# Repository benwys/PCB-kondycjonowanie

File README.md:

# PCB-kondycjonowanie
Projekt układu kondycjonowania sygnałów pomiarowych dla falownika napięcia

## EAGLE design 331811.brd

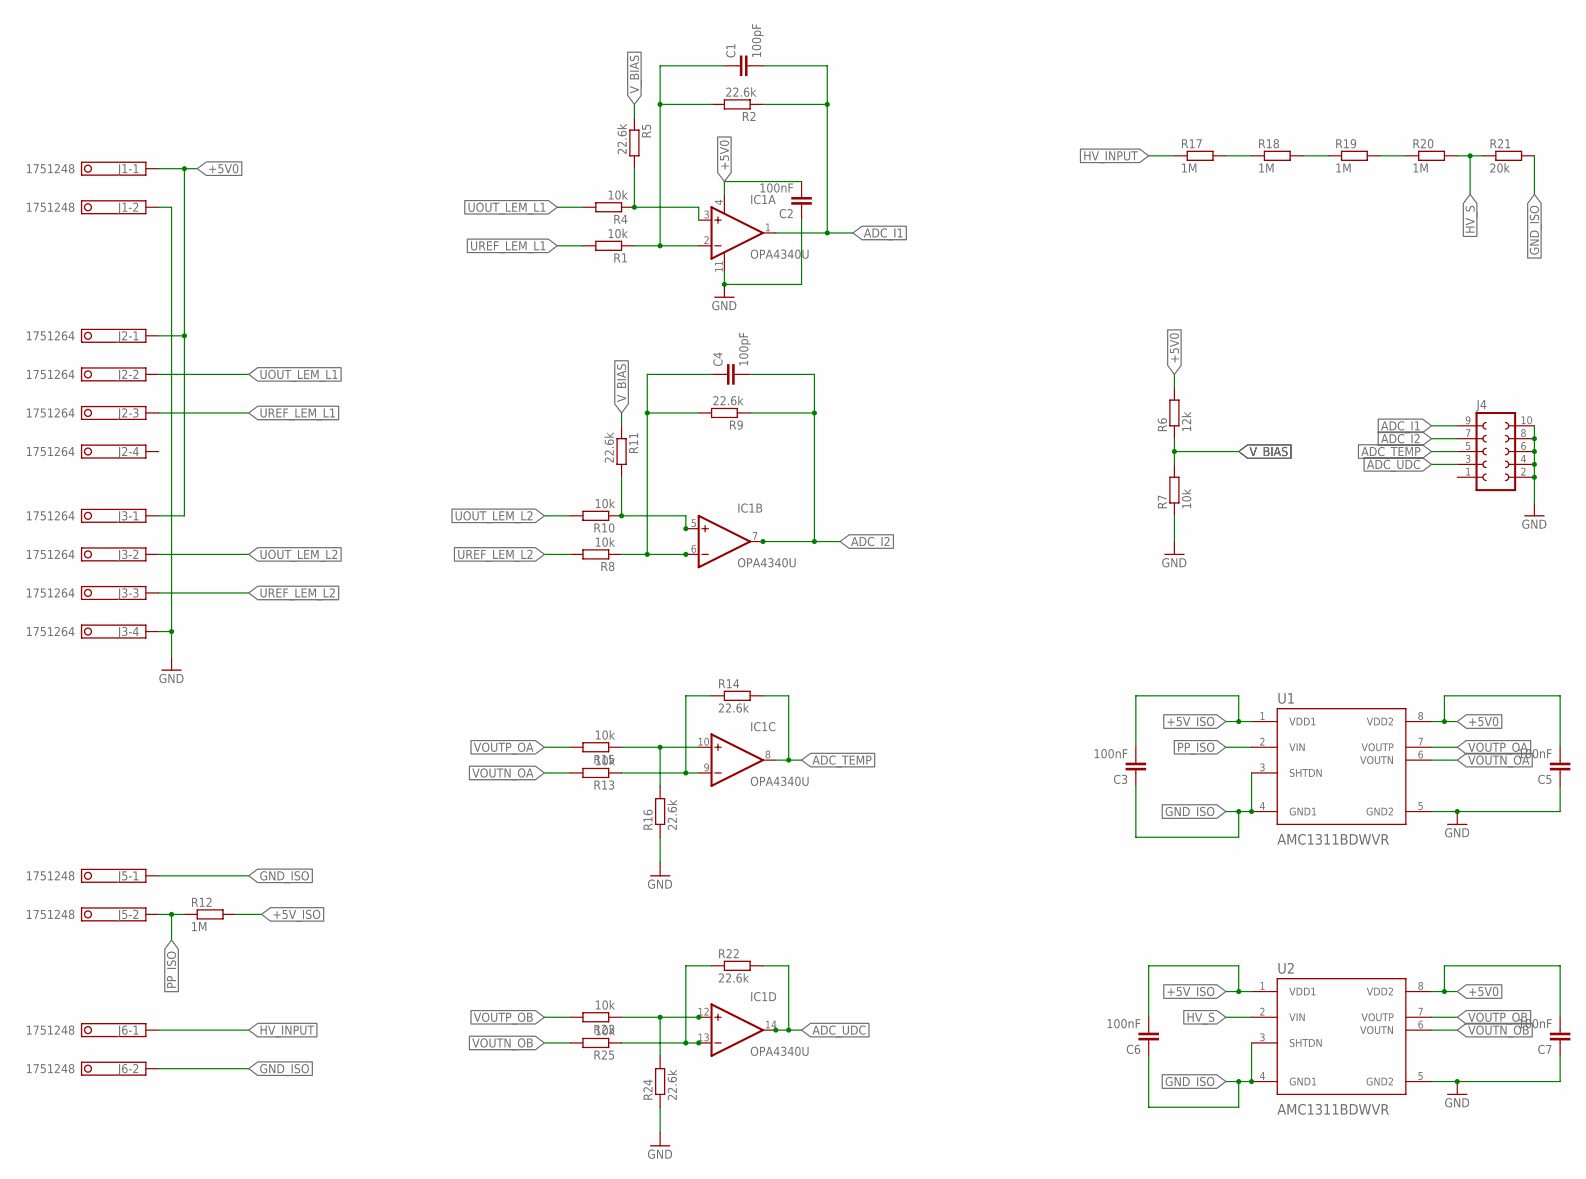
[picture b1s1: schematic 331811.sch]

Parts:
C1, C4: 100pF; C0805
C2, C3, C5, C6, C7: 100nF; C0805
IC1: OPA4340U; SO14
J1, J5, J6: 1751248
J2, J3: 1751264
J4: FE05-2
R1, R4, R7, R8, R10, R13, R15, R23, R25: 10k; M1206
R2, R5, R9, R11, R14, R16, R22, R24: 22.6k; M1206
R6: 12k; M1206
R12, R17, R18, R19, R20: 1M; M1206
R21: 20k; M1206
U1, U2: AMC1311BDWVR; SOIC127P1150X280-8N

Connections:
+5V0: C2.2, C5.2, C7.2, IC1.4 (V+), J1.1, J2.1, J3.1, R6.2, U1.8 (VDD2), U2.8 (VDD2)
+5V_ISO: C3.2, C6.2, R12.2, U1.1 (VDD1), U2.1 (VDD1)
ADC_I1: C1.2, IC1.1 (OUT), J4.9, R2.1
ADC_I2: C4.2, IC1.7 (OUT), J4.7, R9.1
ADC_TEMP: IC1.8 (OUT), J4.5, R14.2
ADC_UDC: IC1.14 (OUT), J4.3, R22.2
GND: C2.1, C5.1, C7.1, IC1.11 (V-), J1.2, J3.4, J4.2, J4.4, J4.6, J4.8, J4.10, R7.1, R16.1, R24.1, U1.5 (GND2), U2.5 (GND2)
GND_ISO: C3.1, C6.1, J5.1, J6.2, R21.2, U1.3 (SHTDN), U1.4 (GND1), U2.3 (SHTDN), U2.4 (GND1)
HV_INPUT: J6.1, R17.1
HV_S: R20.2, R21.1, U2.2 (VIN)
unnamed: C4.1, IC1.6 (-IN), R8.1, R9.2
unnamed: IC1.5 (+IN), R10.1, R11.2
unnamed: C1.1, IC1.2 (-IN), R1.1, R2.2
unnamed: IC1.9 (-IN), R13.1, R14.1
unnamed: IC1.3 (+IN), R4.1, R5.2
unnamed: IC1.10 (+IN), R15.1, R16.2
unnamed: R17.2, R18.1
unnamed: R18.2, R19.1
unnamed: R19.2, R20.1
unnamed: IC1.13 (-IN), R22.1, R25.1
unnamed: IC1.12 (+IN), R23.1, R24.2
PP_ISO: J5.2, R12.1, U1.2 (VIN)
UOUT_LEM_L1: J2.2
UOUT_LEM_L2: J3.2
UREF_LEM_L1: J2.3, R1.2
UREF_LEM_L2: J3.3, R8.2
VOUTN_OA: R13.2, U1.6 (VOUTN)
VOUTN_OB: R25.2, U2.6 (VOUTN)
VOUTP_OA: R15.2, U1.7 (VOUTP)
VOUTP_OB: R23.2, U2.7 (VOUTP)
V_BIAS: R5.1, R6.1, R7.2, R11.1

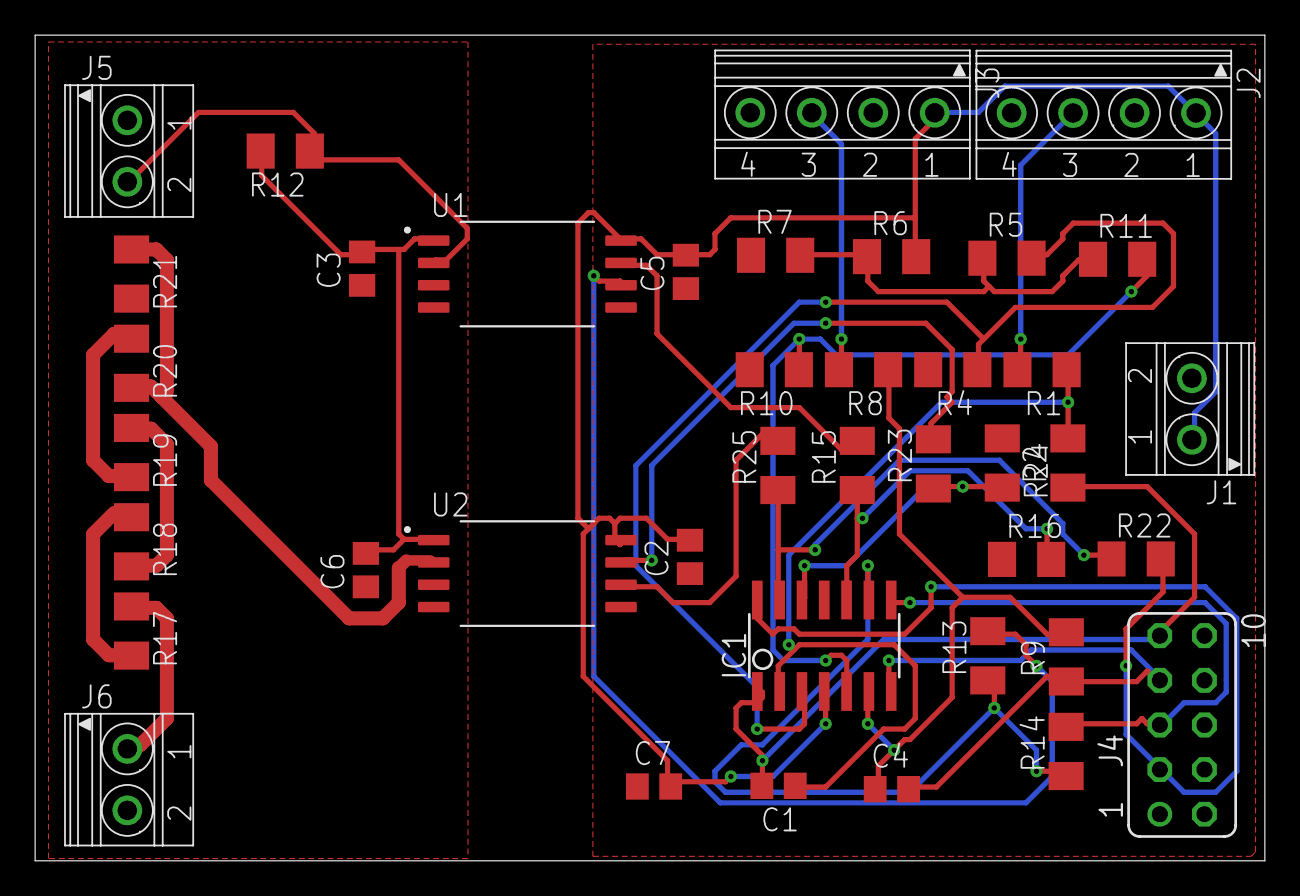
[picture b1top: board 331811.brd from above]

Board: 2 copper layers, 70.0 x 47.0 mm, 40 parts (0 on the bottom side), 29 nets.

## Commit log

2026-05-14 Projekt płytki do kondycjonowania sygnałów
